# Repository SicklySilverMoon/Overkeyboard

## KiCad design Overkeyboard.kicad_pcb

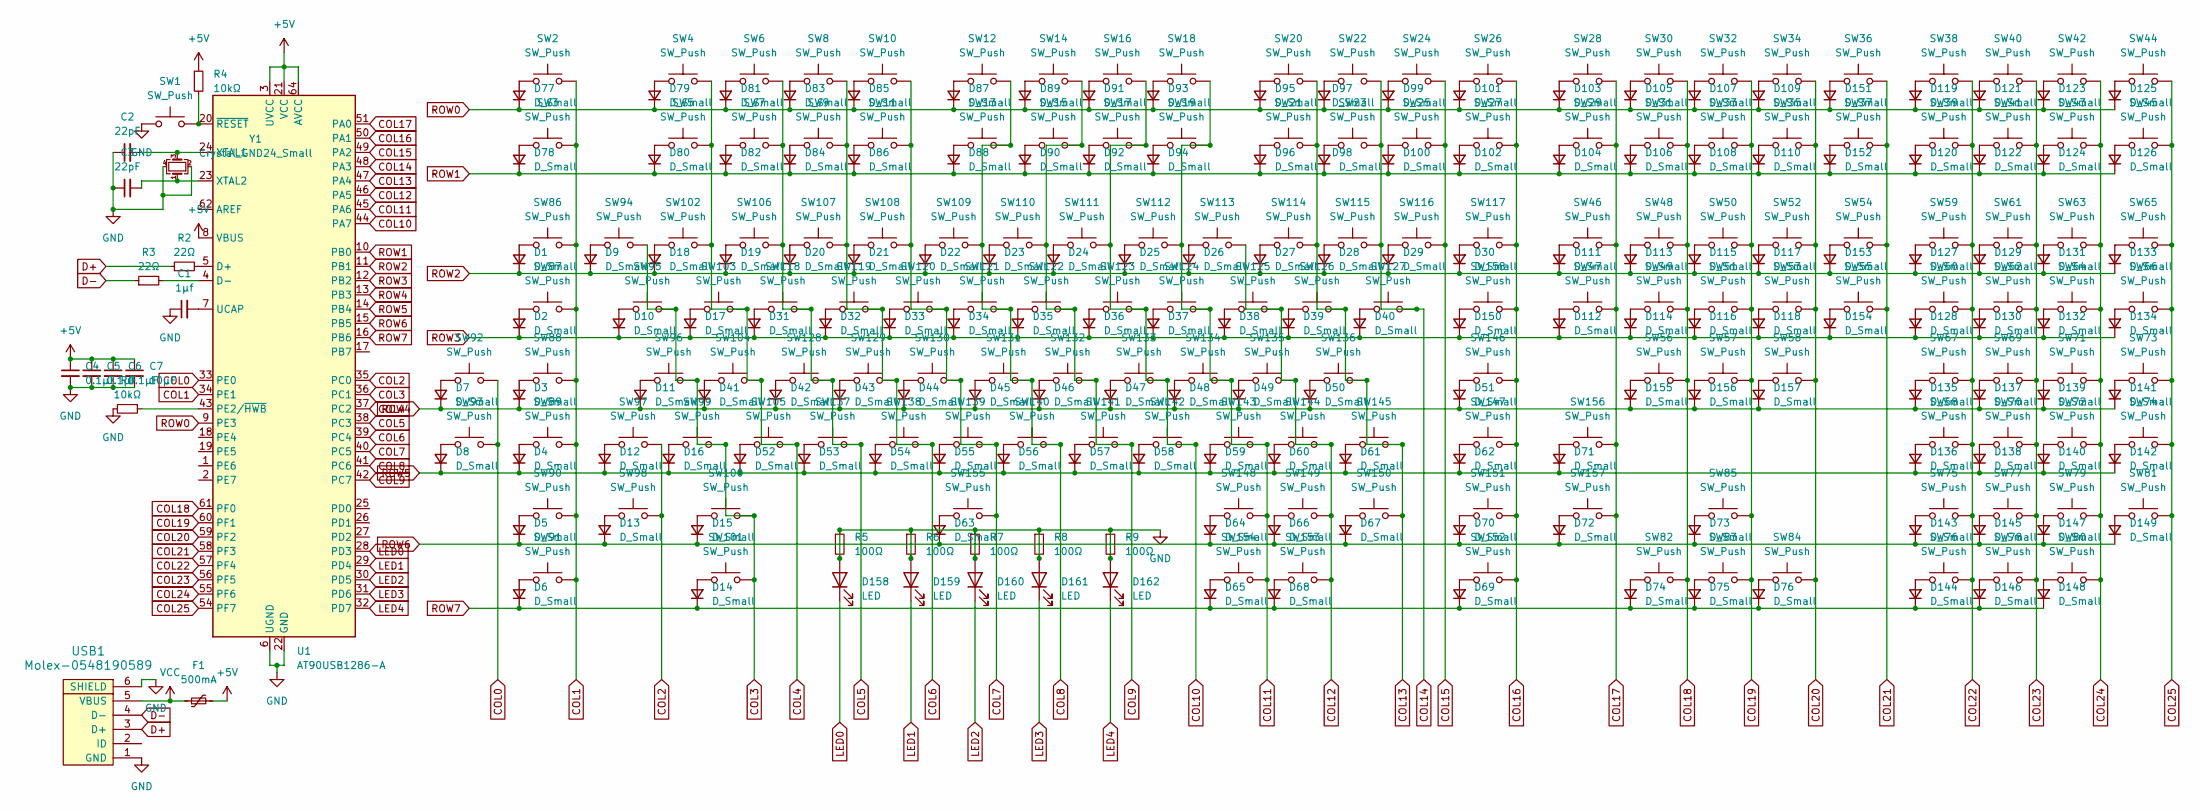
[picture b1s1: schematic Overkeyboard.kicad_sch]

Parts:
C1: 1μf; C_0805_2012Metric_Pad1.18x1.45mm_HandSolder
C2, C3: 22pF; C_0805_2012Metric_Pad1.18x1.45mm_HandSolder
C4, C5, C6: 0.1μF; C_0805_2012Metric_Pad1.18x1.45mm_HandSolder
C7: 10μF; C_0805_2012Metric_Pad1.18x1.45mm_HandSolder
D1, D2, D3, D4, D5, D6, D7, D8, D9, D10, D11, D12, D13, D14, D15, D16, D17, D18, D19, D20, D21, D22, D23, D24, D25, D26, D27, D28, D29, D30, D31, D32, D33, D34, D35, D36, D37, D38, D39, D40, D41, D42, D43, D44, D45, D46, D47, D48, D49, D50, D51, D52, D53, D54, D55, D56, D57, D58, D59, D60, D61, D62, D63, D64, D65, D66, D67, D68, D69, D70, D71, D72, D73, D74, D75, D76, D77, D78, D79, D80, D81, D82, D83, D84, D85, D86, D87, D88, D89, D90, D91, D92, D93, D94, D95, D96, D97, D98, D99, D100, D101, D102, D103, D104, D105, D106, D107, D108, D109, D110, D111, D112, D113, D114, D115, D116, D117, D118, D119, D120, D121, D122, D123, D124, D125, D126, D127, D128, D129, D130, D131, D132, D133, D134, D135, D136, D137, D138, D139, D140, D141, D142, D143, D144, D145, D146, D147, D148, D149, D150, D151, D152, D153, D154, D155, D156, D157: D_Small; D_SOD-123
D158, D159, D160, D161, D162: LED; LED_D5.0mm
F1: 500mA; Fuse_1206_3216Metric_Pad1.42x1.75mm_HandSolder
R1, R4: 10kΩ; R_0805_2012Metric_Pad1.20x1.40mm_HandSolder
R2, R3: 22Ω; R_0805_2012Metric_Pad1.20x1.40mm_HandSolder
R5, R6, R7, R8, R9: 100Ω; R_0805_2012Metric_Pad1.20x1.40mm_HandSolder
SW1: SW_Push; SKQG-1155865
SW2, SW3, SW4, SW5, SW6, SW7, SW8, SW9, SW10, SW11, SW12, SW13, SW14, SW15, SW16, SW17, SW18, SW19, SW20, SW21, SW22, SW23, SW24, SW25, SW26, SW27, SW28, SW29, SW30, SW31, SW32, SW33, SW34, SW35, SW36, SW37, SW38, SW39, SW40, SW41, SW42, SW43, SW44, SW45, SW46, SW47, SW48, SW49, SW50, SW51, SW52, SW53, SW54, SW55, SW56, SW57, SW58, SW59, SW60, SW61, SW62, SW63, SW64, SW65, SW66, SW67, SW68, SW69, SW70, SW71, SW72, SW73, SW74, SW75, SW76, SW77, SW78, SW79, SW80, SW82, SW83, SW84, SW85, SW86, SW94, SW95, SW96, SW97, SW99, SW102, SW103, SW104, SW105, SW106, SW107, SW108, SW109, SW110, SW111, SW112, SW113, SW114, SW115, SW116, SW117, SW118, SW119, SW120, SW121, SW122, SW123, SW124, SW125, SW126, SW127, SW128, SW129, SW130, SW131, SW132, SW133, SW134, SW135, SW136, SW137, SW138, SW139, SW140, SW141, SW142, SW143, SW144, SW145: SW_Push; MX-Solderable-1U
SW81: SW_Push; MX-Solderable-2U-Vertical
SW87, SW158: SW_Push; MX-Solderable-1.5U
SW88, SW101, SW147, SW152: SW_Push; MX-Solderable-1.75U
SW89, SW90, SW92, SW93, SW98, SW100, SW148, SW149, SW150, SW151, SW154, SW156, SW157: SW_Push; MX-Solderable-1.25U
SW91, SW153: SW_Push; MX-Solderable-2U
SW146: SW_Push; MX-Solderable-2.25U
SW155: SW_Push; MX-Solderable-6.25U
U1: AT90USB1286-A; TQFP-64_14x14mm_P0.8mm
USB1: Molex-0548190589
Y1: Crystal_GND24_Small; Crystal_SMD_3225-4Pin_3.2x2.5mm_HandSoldering

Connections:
+5V: C4.1, C5.1, C6.1, C7.1, F1.2, R4.1, U1.3 (UVCC), U1.8 (VBUS), U1.21 (VCC), U1.52 (VCC), U1.64 (AVCC)
COL0: SW92.1, SW93.1, U1.33 (PE0)
COL1: SW2.1, SW3.1, SW86.1, SW87.1, SW88.1, SW89.1, SW90.1, SW91.1, U1.34 (PE1)
COL2: SW97.1, SW98.1, U1.35 (PC0)
COL3: SW94.1, SW95.1, SW96.1, SW99.1, SW100.1, SW101.1, U1.36 (PC1)
COL4: SW4.1, SW5.1, SW102.1, SW103.1, SW104.1, SW105.1, U1.37 (PC2)
COL5: SW6.1, SW7.1, SW106.1, SW118.1, SW128.1, SW137.1, U1.38 (PC3)
COL6: SW8.1, SW9.1, SW107.1, SW119.1, SW129.1, SW138.1, U1.39 (PC4)
COL7: SW10.1, SW11.1, SW108.1, SW120.1, SW130.1, SW139.1, SW155.1, U1.40 (PC5)
COL8: SW12.1, SW13.1, SW109.1, SW121.1, SW131.1, SW140.1, U1.41 (PC6)
COL9: SW14.1, SW15.1, SW110.1, SW122.1, SW132.1, SW141.1, U1.42 (PC7)
COL10: SW16.1, SW17.1, SW111.1, SW123.1, SW133.1, SW142.1, U1.44 (PA7)
COL11: SW18.1, SW19.1, SW112.1, SW124.1, SW134.1, SW143.1, SW148.1, SW154.1, U1.45 (PA6)
COL12: SW113.1, SW125.1, SW135.1, SW144.1, SW149.1, SW153.1, U1.46 (PA5)
COL13: SW20.1, SW21.1, SW114.1, SW126.1, SW136.1, SW145.1, SW150.1, U1.47 (PA4)
COL14: SW22.1, SW23.1, SW115.1, SW127.1, U1.48 (PA3)
COL15: SW24.1, SW25.1, SW116.1, U1.49 (PA2)
COL16: SW26.1, SW27.1, SW117.1, SW146.1, SW147.1, SW151.1, SW152.1, SW158.1, U1.50 (PA1)
COL17: SW28.1, SW29.1, SW46.1, SW47.1, SW156.1, SW157.1, U1.51 (PA0)
COL18: SW30.1, SW31.1, SW48.1, SW49.1, SW56.1, SW82.1, U1.61 (PF0)
COL19: SW32.1, SW33.1, SW50.1, SW51.1, SW57.1, SW83.1, SW85.1, U1.60 (PF1)
COL20: SW34.1, SW35.1, SW52.1, SW53.1, SW58.1, SW84.1, U1.59 (PF2)
COL21: SW36.1, SW37.1, SW54.1, SW55.1, U1.58 (PF3)
COL22: SW38.1, SW39.1, SW59.1, SW60.1, SW67.1, SW68.1, SW75.1, SW76.1, U1.57 (PF4)
COL23: SW40.1, SW41.1, SW61.1, SW62.1, SW69.1, SW70.1, SW77.1, SW78.1, U1.56 (PF5)
COL24: SW42.1, SW43.1, SW63.1, SW64.1, SW71.1, SW72.1, SW79.1, SW80.1, U1.55 (PF6)
COL25: SW44.1, SW45.1, SW65.1, SW66.1, SW73.1, SW74.1, SW81.1, U1.54 (PF7)
D+: R2.1, USB1.3 (D+)
D-: R3.1, USB1.4 (D-)
GND: C1.1, C2.1, C3.1, C4.2, C5.2, C6.2, C7.2, D158.2 (A), D159.2 (A), D160.2 (A), D161.2 (A), D162.2 (A), R1.2, R5.1, R5.2, R6.1, R6.2, R7.1, R7.2, R8.1, R8.2, R9.1, R9.2, SW1.1, U1.6 (UGND), U1.22 (GND), U1.53 (GND), U1.63 (GND), USB1.1 (GND), USB1.6 (SHIELD), Y1.2, Y1.4
LED0: D158.1 (K), U1.28 (PD3)
LED1: D159.1 (K), U1.29 (PD4)
LED2: D160.1 (K), U1.30 (PD5)
LED3: D161.1 (K), U1.31 (PD6)
LED4: D162.1 (K), U1.32 (PD7)
unnamed: D1.2 (A), SW86.2
unnamed: D2.2 (A), SW87.2
unnamed: D3.2 (A), SW88.2
unnamed: D4.2 (A), SW89.2
unnamed: D5.2 (A), SW90.2
unnamed: D6.2 (A), SW91.2
unnamed: D7.2 (A), SW92.2
unnamed: D8.2 (A), SW93.2
unnamed: D9.2 (A), SW94.2
unnamed: D10.2 (A), SW95.2
unnamed: D11.2 (A), SW96.2
unnamed: D12.2 (A), SW97.2
unnamed: D13.2 (A), SW98.2
unnamed: D14.2 (A), SW101.2
unnamed: D15.2 (A), SW100.2
unnamed: D16.2 (A), SW99.2
unnamed: D17.2 (A), SW103.2
unnamed: D18.2 (A), SW102.2
unnamed: D19.2 (A), SW106.2
unnamed: D20.2 (A), SW107.2
unnamed: D21.2 (A), SW108.2
unnamed: D22.2 (A), SW109.2
unnamed: D23.2 (A), SW110.2
unnamed: D24.2 (A), SW111.2
unnamed: D25.2 (A), SW112.2
unnamed: D26.2 (A), SW113.2
unnamed: D27.2 (A), SW114.2
unnamed: D28.2 (A), SW115.2
unnamed: D29.2 (A), SW116.2
unnamed: D30.2 (A), SW117.2
unnamed: D31.2 (A), SW118.2
unnamed: D32.2 (A), SW119.2
unnamed: D33.2 (A), SW120.2
unnamed: D34.2 (A), SW121.2
unnamed: D35.2 (A), SW122.2
unnamed: D36.2 (A), SW123.2
unnamed: D37.2 (A), SW124.2
unnamed: D38.2 (A), SW125.2
unnamed: D39.2 (A), SW126.2
unnamed: D40.2 (A), SW127.2
unnamed: D41.2 (A), SW104.2
unnamed: D42.2 (A), SW128.2
unnamed: D43.2 (A), SW129.2
unnamed: D44.2 (A), SW130.2
unnamed: D45.2 (A), SW131.2
unnamed: D46.2 (A), SW132.2
unnamed: D47.2 (A), SW133.2
unnamed: D48.2 (A), SW134.2
unnamed: D49.2 (A), SW135.2
unnamed: D50.2 (A), SW136.2
unnamed: D51.2 (A), SW146.2
unnamed: D52.2 (A), SW105.2
unnamed: D53.2 (A), SW137.2
unnamed: D54.2 (A), SW138.2
unnamed: D55.2 (A), SW139.2
unnamed: D56.2 (A), SW140.2
unnamed: D57.2 (A), SW141.2
unnamed: D58.2 (A), SW142.2
unnamed: D59.2 (A), SW143.2
unnamed: D60.2 (A), SW144.2
unnamed: D61.2 (A), SW145.2
unnamed: D62.2 (A), SW147.2
unnamed: D63.2 (A), SW155.2
unnamed: D64.2 (A), SW148.2
unnamed: D65.2 (A), SW154.2
unnamed: D66.2 (A), SW149.2
unnamed: D67.2 (A), SW150.2
unnamed: D68.2 (A), SW153.2
unnamed: D69.2 (A), SW152.2
unnamed: D70.2 (A), SW151.2
unnamed: D71.2 (A), SW156.2
unnamed: D72.2 (A), SW157.2
unnamed: D73.2 (A), SW85.2
unnamed: D74.2 (A), SW82.2
unnamed: D75.2 (A), SW83.2
unnamed: D76.2 (A), SW84.2
unnamed: D77.2 (A), SW2.2
unnamed: D78.2 (A), SW3.2
unnamed: D79.2 (A), SW4.2
unnamed: D80.2 (A), SW5.2
unnamed: D81.2 (A), SW6.2
unnamed: D82.2 (A), SW7.2
unnamed: D83.2 (A), SW8.2
unnamed: D84.2 (A), SW9.2
unnamed: D85.2 (A), SW10.2
unnamed: D86.2 (A), SW11.2
unnamed: D87.2 (A), SW12.2
unnamed: D88.2 (A), SW13.2
unnamed: D89.2 (A), SW14.2
unnamed: D90.2 (A), SW15.2
unnamed: D91.2 (A), SW16.2
unnamed: D92.2 (A), SW17.2
unnamed: D93.2 (A), SW18.2
unnamed: D94.2 (A), SW19.2
unnamed: D95.2 (A), SW20.2
unnamed: D96.2 (A), SW21.2
unnamed: D97.2 (A), SW22.2
unnamed: D98.2 (A), SW23.2
unnamed: D99.2 (A), SW24.2
unnamed: D100.2 (A), SW25.2
unnamed: D101.2 (A), SW26.2
unnamed: D102.2 (A), SW27.2
unnamed: D103.2 (A), SW28.2
unnamed: D104.2 (A), SW29.2
unnamed: D105.2 (A), SW30.2
unnamed: D106.2 (A), SW31.2
unnamed: D107.2 (A), SW32.2
unnamed: D108.2 (A), SW33.2
unnamed: D109.2 (A), SW34.2
unnamed: D110.2 (A), SW35.2
unnamed: D111.2 (A), SW46.2
unnamed: D112.2 (A), SW47.2
unnamed: D113.2 (A), SW48.2
unnamed: D114.2 (A), SW49.2
unnamed: D115.2 (A), SW50.2
unnamed: D116.2 (A), SW51.2
unnamed: D117.2 (A), SW52.2
unnamed: D118.2 (A), SW53.2
unnamed: D119.2 (A), SW38.2
unnamed: D120.2 (A), SW39.2
unnamed: D121.2 (A), SW40.2
unnamed: D122.2 (A), SW41.2
unnamed: D123.2 (A), SW42.2
unnamed: D124.2 (A), SW43.2
unnamed: D125.2 (A), SW44.2
unnamed: D126.2 (A), SW45.2
unnamed: D127.2 (A), SW59.2
unnamed: D128.2 (A), SW60.2
unnamed: D129.2 (A), SW61.2
unnamed: D130.2 (A), SW62.2
unnamed: D131.2 (A), SW63.2
unnamed: D132.2 (A), SW64.2
unnamed: D133.2 (A), SW65.2
unnamed: D134.2 (A), SW66.2
unnamed: D135.2 (A), SW67.2
unnamed: D136.2 (A), SW68.2
unnamed: D137.2 (A), SW69.2
unnamed: D138.2 (A), SW70.2
unnamed: D139.2 (A), SW71.2
unnamed: D140.2 (A), SW72.2
unnamed: D141.2 (A), SW73.2
unnamed: D142.2 (A), SW74.2
unnamed: D143.2 (A), SW75.2
unnamed: D144.2 (A), SW76.2
unnamed: D145.2 (A), SW77.2
unnamed: D146.2 (A), SW78.2
unnamed: D147.2 (A), SW79.2
unnamed: D148.2 (A), SW80.2
unnamed: D149.2 (A), SW81.2
unnamed: D150.2 (A), SW158.2
unnamed: D151.2 (A), SW36.2
unnamed: D152.2 (A), SW37.2
unnamed: D153.2 (A), SW54.2
unnamed: D154.2 (A), SW55.2
unnamed: D155.2 (A), SW56.2
unnamed: D156.2 (A), SW57.2
unnamed: D157.2 (A), SW58.2
unnamed: R2.2, U1.5 (D+)
unnamed: R3.2, U1.4 (D-)
unnamed: R1.1, U1.43 (PE2/~HWB)
unnamed: C1.2, U1.7 (UCAP)
unnamed: C2.2, U1.24 (XTAL1), Y1.3
unnamed: C3.2, U1.23 (XTAL2), Y1.1
unnamed: R4.2, SW1.2, U1.20 (~RESET)
ROW0: D77.1 (K), D79.1 (K), D81.1 (K), D83.1 (K), D85.1 (K), D87.1 (K), D89.1 (K), D91.1 (K), D93.1 (K), D95.1 (K), D97.1 (K), D99.1 (K), D101.1 (K), D103.1 (K), D105.1 (K), D107.1 (K), D109.1 (K), D119.1 (K), D121.1 (K), D123.1 (K), D125.1 (K), D151.1 (K), U1.9 (PE3)
ROW1: D78.1 (K), D80.1 (K), D82.1 (K), D84.1 (K), D86.1 (K), D88.1 (K), D90.1 (K), D92.1 (K), D94.1 (K), D96.1 (K), D98.1 (K), D100.1 (K), D102.1 (K), D104.1 (K), D106.1 (K), D108.1 (K), D110.1 (K), D120.1 (K), D122.1 (K), D124.1 (K), D126.1 (K), D152.1 (K), U1.10 (PB0)
ROW2: D1.1 (K), D9.1 (K), D18.1 (K), D19.1 (K), D20.1 (K), D21.1 (K), D22.1 (K), D23.1 (K), D24.1 (K), D25.1 (K), D26.1 (K), D27.1 (K), D28.1 (K), D29.1 (K), D30.1 (K), D111.1 (K), D113.1 (K), D115.1 (K), D117.1 (K), D127.1 (K), D129.1 (K), D131.1 (K), D133.1 (K), D153.1 (K), U1.11 (PB1)
ROW3: D2.1 (K), D10.1 (K), D17.1 (K), D31.1 (K), D32.1 (K), D33.1 (K), D34.1 (K), D35.1 (K), D36.1 (K), D37.1 (K), D38.1 (K), D39.1 (K), D40.1 (K), D112.1 (K), D114.1 (K), D116.1 (K), D118.1 (K), D128.1 (K), D130.1 (K), D132.1 (K), D134.1 (K), D150.1 (K), D154.1 (K), U1.12 (PB2)
ROW4: D3.1 (K), D7.1 (K), D11.1 (K), D41.1 (K), D42.1 (K), D43.1 (K), D44.1 (K), D45.1 (K), D46.1 (K), D47.1 (K), D48.1 (K), D49.1 (K), D50.1 (K), D51.1 (K), D135.1 (K), D137.1 (K), D139.1 (K), D141.1 (K), D155.1 (K), D156.1 (K), D157.1 (K), U1.13 (PB3)
ROW5: D4.1 (K), D8.1 (K), D12.1 (K), D16.1 (K), D52.1 (K), D53.1 (K), D54.1 (K), D55.1 (K), D56.1 (K), D57.1 (K), D58.1 (K), D59.1 (K), D60.1 (K), D61.1 (K), D62.1 (K), D71.1 (K), D136.1 (K), D138.1 (K), D140.1 (K), D142.1 (K), U1.14 (PB4)
ROW6: D5.1 (K), D13.1 (K), D15.1 (K), D63.1 (K), D64.1 (K), D66.1 (K), D67.1 (K), D70.1 (K), D72.1 (K), D73.1 (K), D143.1 (K), D145.1 (K), D147.1 (K), D149.1 (K), U1.15 (PB5)
ROW7: D6.1 (K), D14.1 (K), D65.1 (K), D68.1 (K), D69.1 (K), D74.1 (K), D75.1 (K), D76.1 (K), D144.1 (K), D146.1 (K), D148.1 (K), U1.16 (PB6)
VCC: F1.1, USB1.5 (VBUS)

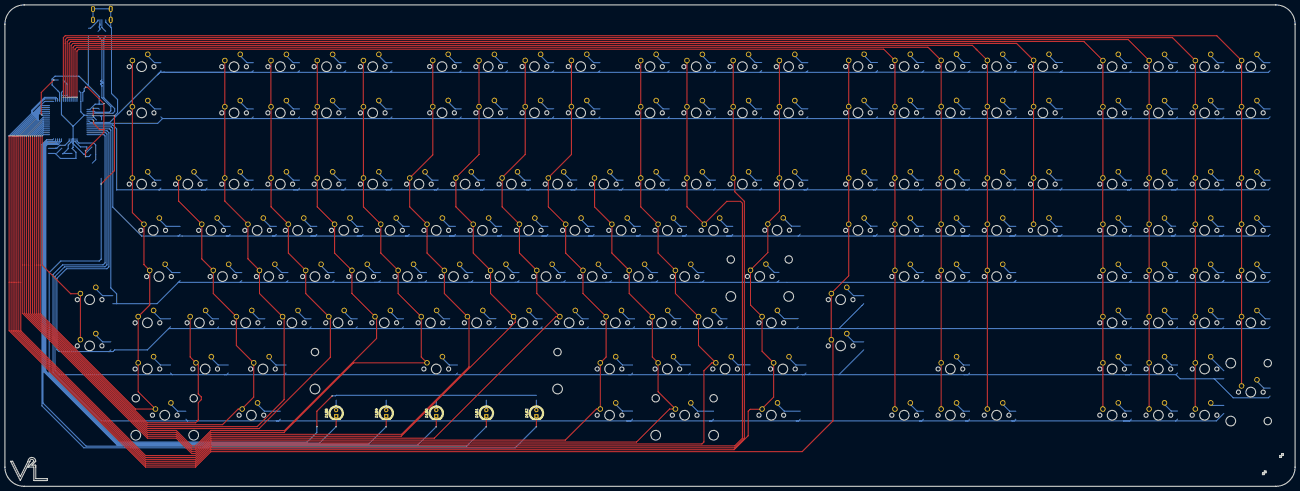
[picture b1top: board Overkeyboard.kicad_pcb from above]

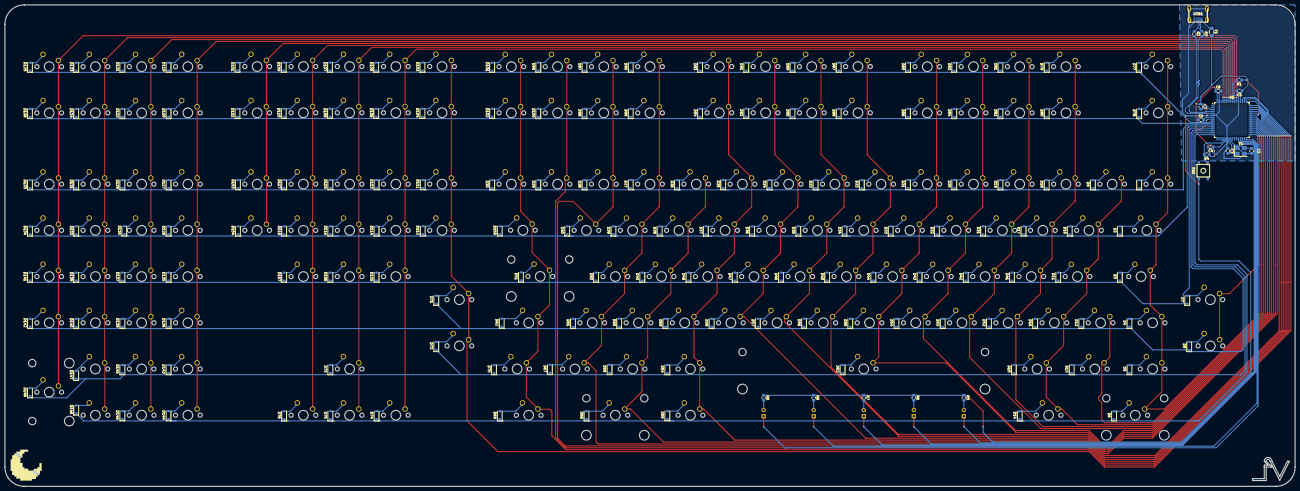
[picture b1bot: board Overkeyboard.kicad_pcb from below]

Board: 2 copper layers, 531.8 x 198.4 mm, 340 parts (178 on the bottom side), 208 nets.

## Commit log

2024-05-18 start
2024-05-18 add submods
2024-05-19 part of schematic done
2024-05-19 added footprints
2024-05-19 outline is starting to be built
2024-05-20 It should be fully wired now
2024-05-22 Almost fully wired excepting figuring out what LED and resistor values to use
2024-05-23 slight wiring changes and LED resistor values determined
2024-07-15 fix some minor positional differences
